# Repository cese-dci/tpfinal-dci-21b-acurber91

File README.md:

## Trabajo Práctico Final de la asignatura DCI ##

Este repositorio contiene el Trabajo Práctico Final de la asignatura de Diseño de Circuitos Impresos de la carrera Maestría en Internet de las Cosas (MIoT) de la FIUBA.

* **Autor**: Agustín Curcio Berardi
* **Revisor**: Gustavo Zocco
* **Docente**: Diego Brengui
* **Título del Trabajo**:  Adafruit Feather M0 with LoRa Radio Module Adaptation
* **Descripción**:  Plataforma modular Feather desarrollada por Adafruit con el mismo concepto de las placas Arduino. Existen diversas placas con un mismo formato físico y diferente hardware montado. Esta versión en particular incorpora un microcontrolador ARM Cortex-M0 junto con un módulo LoRa basado en el chipset SX1276 de la empresa Semtech.

<p align="center">
    <br>
    <b>Figura 1</b>. Vista isométrica superior de la adaptación realizada. 
</p>

<p align="center">
    <br>
    <b>Figura 2</b>. Vista isométrica inferior de la adaptación realizada. 
</p>

<p align="center">
    <br>
    <b>Figura 3</b>. Vista superior de la adaptación realizada. 
</p>

<p align="center">
    <br>
    <b>Figura 4</b>. Vista inferior de la adaptación realizada. 
</p>

## Detalles de la adaptación ##

Este Trabajo Práctico realizó una adaptación de la placa utilizada como propuesta para poder cumplir con los requerimientos establecidos en la materia. Así:

- Se modificaron los tamaños de los componentes pasivos. Se pasó de tamaño 0603 a 0805.
- El cambio de tamaño de los componentes pasivos requirió modificar las dimensiones del circuito impreso. La altura no se modificó para garantizar la compatibilidad con otras placas de la línea Feather. No obstante, sí se modificó el largo total de la misma para hacer lugar a componentes de mayor tamaño. El circuito impreso final es 6,223 mm más largo que el original.
- Se agregó un segundo fiducial que no estaba presente en el diseño original.
- Se adoptó HASL como terminación superficial en lugar de ENIG.

## Licencia de este trabajo ##
Designed by Limor Fried/Ladyada for Adafruit Industries. Creative Commons Attribution/Share-Alike. See License.txt for additional information.

## Estructura ##

El Trabajo Práctico Final tiene la siguiente estructura:

* doc: Toda la información sobre el circuito, principalmente de autoría o procesamiento propio.
  * Notas con cálculos.
  * Fotos de los prototipos.
* info: Toda la información recolectada, principalmente de terceros, como por ejemplo:
  * Hojas de datos.
  * Notas de aplicación.
  * Información de productos comerciales.
* pcb: Archivos de diseño esquemático y PCB.
  * Archivo esquemático en PDF.

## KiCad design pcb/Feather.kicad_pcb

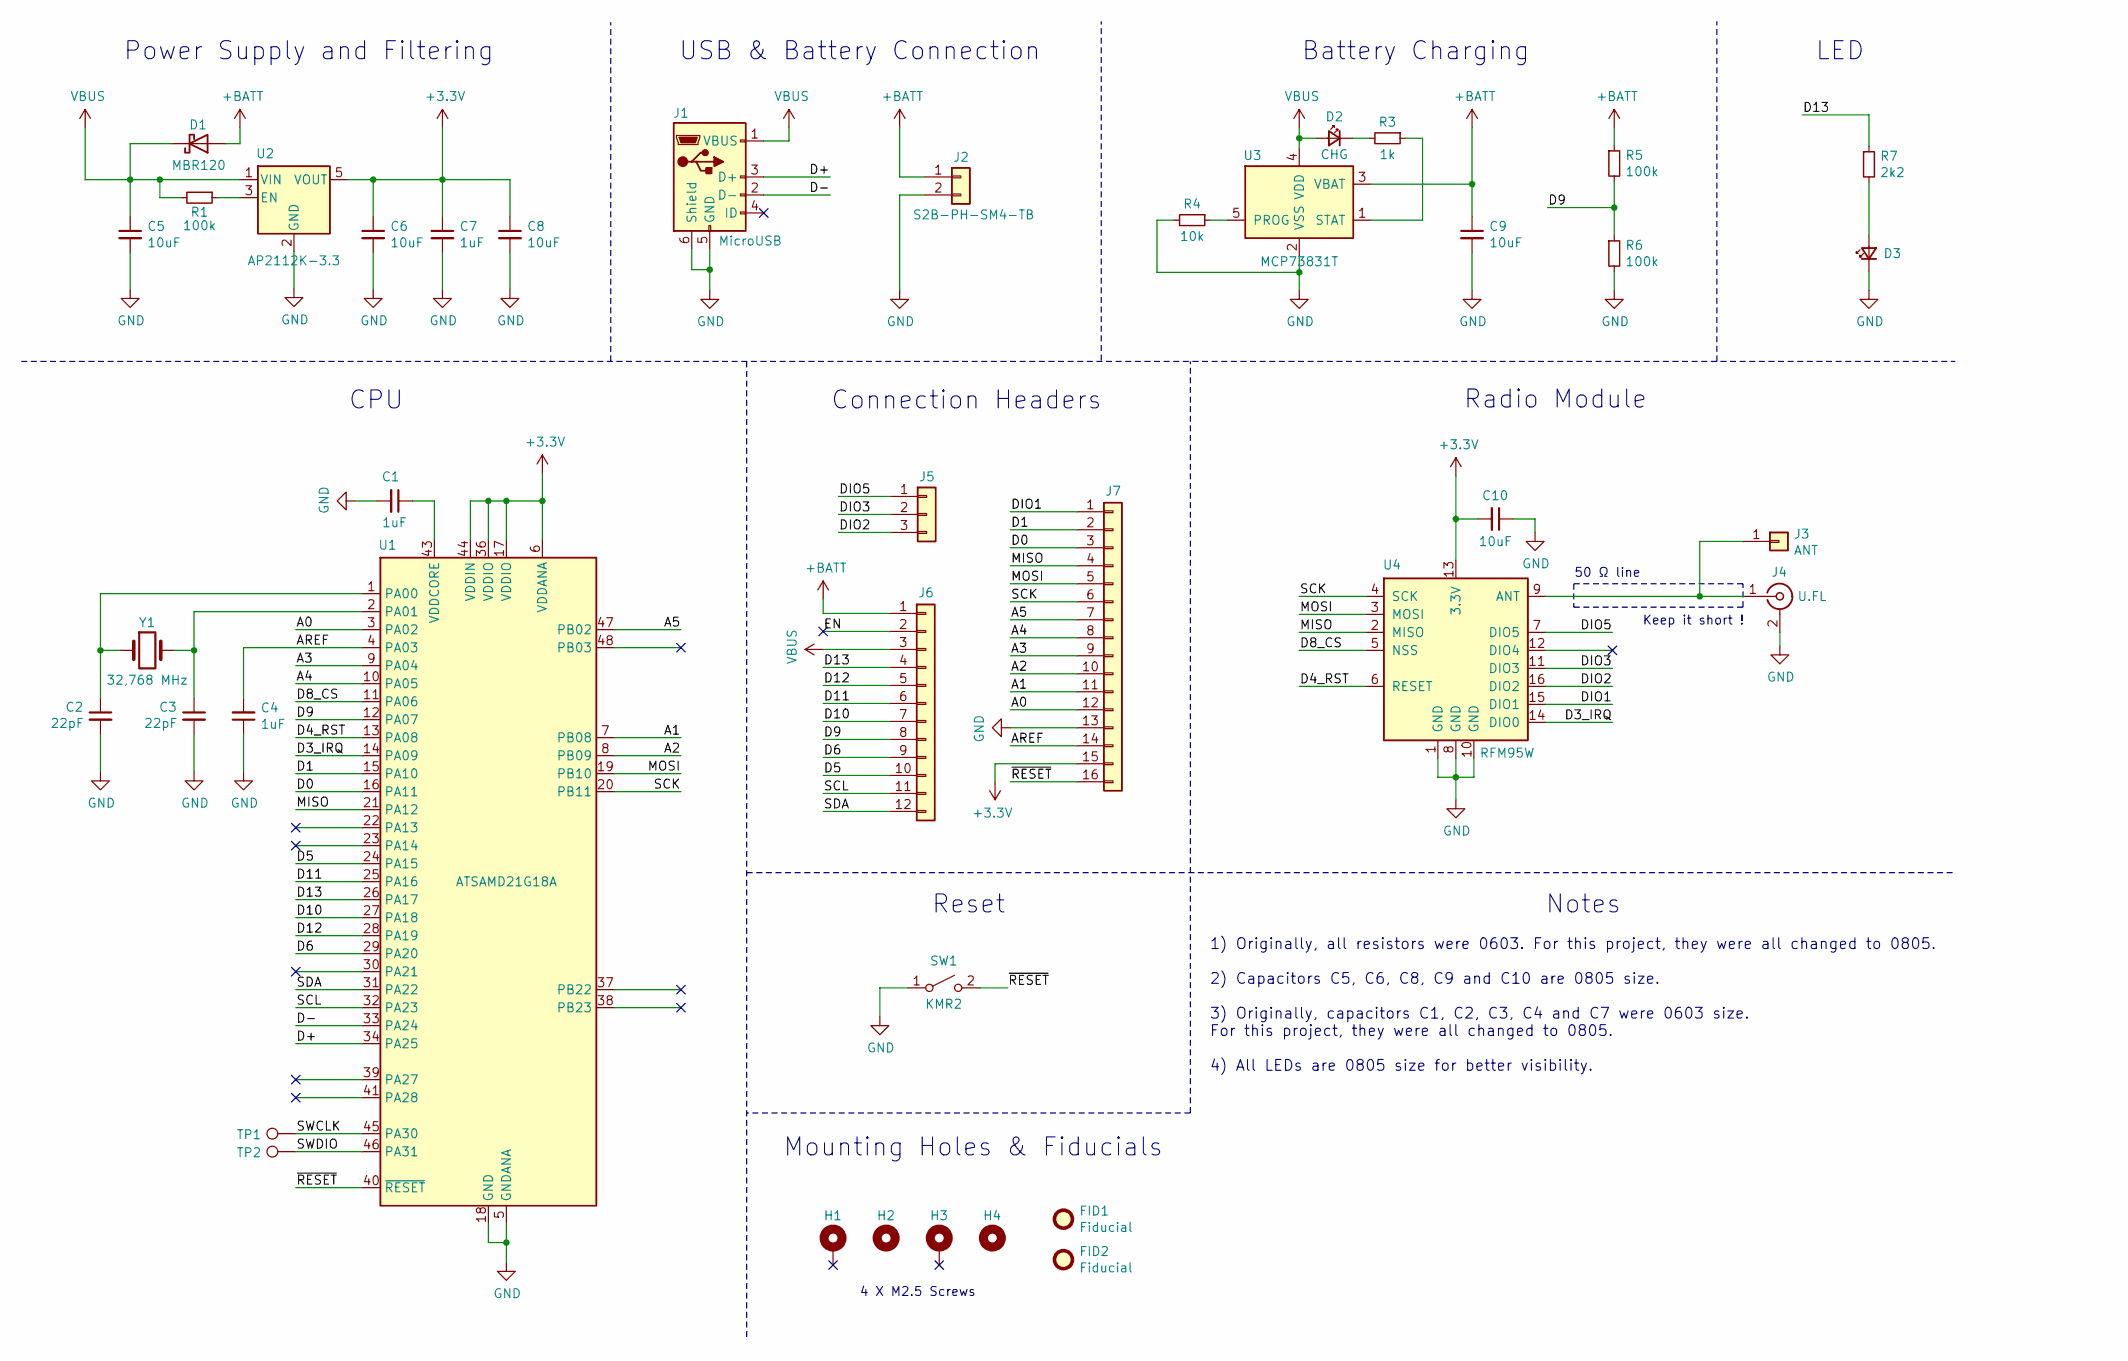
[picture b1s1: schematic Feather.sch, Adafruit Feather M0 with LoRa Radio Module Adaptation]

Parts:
C1, C4, C7: 1uF; C_0805_2012Metric
C2, C3: 22pF; C_0805_2012Metric
C5, C6, C8, C9, C10: 10uF; C_0805_2012Metric
D1: MBR120; D_SOD-123F
D2: CHG; LED_0805_2012Metric_Castellated
D3: PWR; LED_0805_2012Metric_Castellated
FID1, FID2: Fiducial; Fiducial_1mm_Mask2mm
H1, H3: Mounting Hole w/Pad; MountingHole_2.5mm_Pad_TopOnly
H2, H4: Mounting Hole; MountingHole_2.5mm
J1: MicroUSB; USB_Micro-B_Amphenol_10103594-0001LF_Horizontal
J2: S2B-PH-SM4-TB; JST_PH_S2B-PH-SM4-TB_1x02-1MP_P2.00mm_Horizontal
J3: ANT; Adafruit_Feather_PinHeader_1x01_P2.54mm
J4: U.FL; U.FL_Hirose_U.FL-R-SMT-1_Vertical
J5: Conn_01x03; Adafruit_Feather_PinHeader_1x03_P2.54mm
J6: Conn_01x12; Adafruit_Feather_PinHeader_1x12_P2.54mm
J7: Conn_01x16; Adafruit_Feather_PinHeader_1x16_P2.54mm
R1, R5, R6: 100k; R_0805_2012Metric
R3: 1k; R_0805_2012Metric
R4: 10k; R_0805_2012Metric
R7: 2k2; R_0805_2012Metric
SW1: KMR2; SW_Push_1P1T_NO_CK_KMR2
TP1, TP2: TestPoint; TestPoint_Pad_D1.5mm
U1: ATSAMD21G18A; QFN-48-1EP_7x7mm_P0.5mm_EP5.15x5.15mm
U2: AP2112K-3.3; SOT-23-5
U3: MCP73831T; SOT-23-5
U4: RFM95W; HOPERF_RFM9XW_SMD
Y1: 32,768 MHz; Crystal_SMD_3215-2Pin_3.2x1.5mm

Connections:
+3V3: C6.1, C7.1, C8.1, C10.2, J7.15, U1.6 (VDDANA), U1.17 (VDDIO), U1.36 (VDDIO), U1.44 (VDDIN), U2.5 (VOUT), U4.13 (3.3V)
+BATT: C9.1, D1.2 (A), J2.1, J6.1, R5.1, U3.3 (VBAT)
/A0: J7.12, U1.3 (PA02)
/A1: J7.11, U1.7 (PB08)
/A2: J7.10, U1.8 (PB09)
/A3: J7.9, U1.9 (PA04)
/A4: J7.8, U1.10 (PA05)
/A5: J7.7, U1.47 (PB02)
/AREF: C4.2, J7.14, U1.4 (PA03)
/D0: J7.3, U1.16 (PA11)
/D1: J7.2, U1.15 (PA10)
/D3_IRQ: U1.14 (PA09), U4.14 (DIO0)
/D4_RST: U1.13 (PA08), U4.6 (RESET)
/D5: J6.10, U1.24 (PA15)
/D6: J6.9, U1.29 (PA20)
/D8_CS: U1.11 (PA06), U4.5 (NSS)
/D9: J6.8, R5.2, R6.1, U1.12 (PA07)
/D10: J6.7, U1.27 (PA18)
/D11: J6.6, U1.25 (PA16)
/D12: J6.5, U1.28 (PA19)
/D13: J6.4, R7.1, U1.26 (PA17)
/D+: J1.3 (D+), U1.34 (PA25)
/D-: J1.2 (D-), U1.33 (PA24)
/DIO1: J7.1, U4.15 (DIO1)
/DIO2: J5.3, U4.16 (DIO2)
/DIO3: J5.2, U4.11 (DIO3)
/DIO5: J5.1, U4.7 (DIO5)
/EN: J6.2
/MISO: J7.4, U1.21 (PA12), U4.2 (MISO)
/MOSI: J7.5, U1.19 (PB10), U4.3 (MOSI)
/SCK: J7.6, U1.20 (PB11), U4.4 (SCK)
/SCL: J6.11, U1.32 (PA23)
/SDA: J6.12, U1.31 (PA22)
/SWCLK: TP1.1, U1.45 (PA30)
/SWDIO: TP2.1, U1.46 (PA31)
/~RESET: J7.16, SW1.2 (B), U1.40 (~RESET)
GND: C1.2, C2.2, C3.2, C4.1, C5.2, C6.2, C7.2, C8.2, C9.2, C10.1, D3.1 (K), J1.5 (GND), J1.6 (Shield), J2.2, J4.2 (Ext), J7.13, R4.2, R6.2, SW1.1 (A), U1.5 (GNDANA), U1.18 (GND), U1.35 (GND), U1.42 (GND), U1.49 (EP), U2.2 (GND), U3.2 (VSS), U4.1 (GND), U4.8 (GND), U4.10 (GND)
unnamed: C1.1, U1.43 (VDDCORE)
unnamed: C2.1, U1.1 (PA00), Y1.1
unnamed: C3.1, U1.2 (PA01), Y1.2
unnamed: D2.1 (K), R3.2
unnamed: D3.2 (A), R7.2
unnamed: J3.1, J4.1 (In), U4.9 (ANT)
unnamed: R1.1, U2.3 (EN)
unnamed: R3.1, U3.1 (STAT)
unnamed: R4.1, U3.5 (PROG)
VBUS: C5.1, D1.1 (K), D2.2 (A), J1.1 (VBUS), J6.3, R1.2, U2.1 (VIN), U3.4 (VDD)

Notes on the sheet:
USB & Battery Connection
Battery Charging
LED
CPU
Connection Headers
Radio Module
1) Originally, all resistors were 0603. For this project, they were all changed to 0805. 2) Capacitors C5, C6, C8, C9 and C10 are 0805 size. 3) Originally, capacitors C1, C2, C3, C4 and C7 were 0603 size. For this project, they were all changed to 0805. 4) All LEDs are 0805 size for better visibili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
Notes
Keep it short !
50 Ω line
Power Supply and Filtering
Reset
Mounting Holes & Fiducials
4 X M2.5 Screws

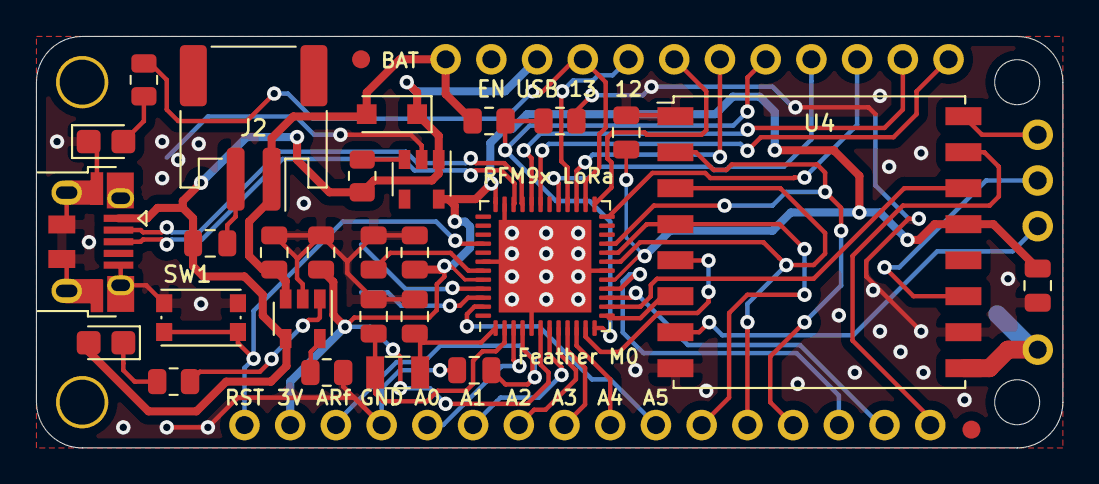
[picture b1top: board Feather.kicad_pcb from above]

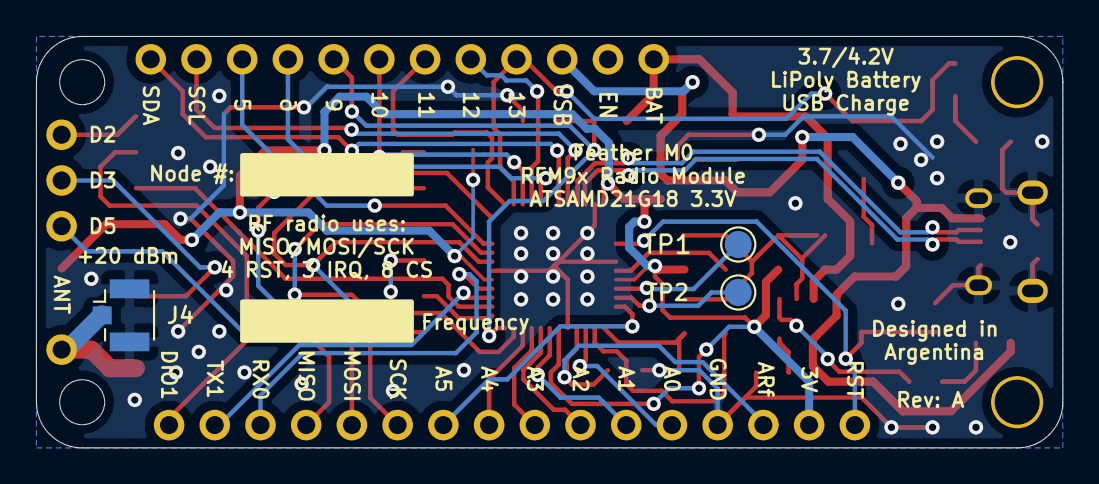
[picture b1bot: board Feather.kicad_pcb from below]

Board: 2 copper layers, 57.0 x 22.9 mm, 40 parts (3 on the bottom side), 46 nets.

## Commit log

2021-06-26 En este commit inicial se agrega el esquemático completo de la placa Adafruit Feather M0 junto con las hojas de datos de sus principales componentes.
2021-06-27 Se agregan los modelos 3D que estaban faltando así como también la documentación y hojas de datos faltantes.
2021-06-27 Se crea la biblioteca Adafruit_PinHeader para las tiras de pines que se deben soldar en los costados de la placa. Con esta modificación, se actualizo también el circuito esquemático. Listo para corre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
2021-06-28 Se realizan leves ajustes en el esquemático y se adiciona el archivo de licencia. Listo para revisar.
2021-06-28 Se agrega el esquemático en formato PDF para facilitar su revisión.
2021-07-30 Se modifica todo el proyecto para utilizar componentes 0805 en lugar de 0603 que se usan en el circuito original. Se incorpora archivo del PCB, con componentes posicionados y con modelos 3D incluídos.
2021-08-09 Se hicieron más ajustes para acomodar mejor los componentes tamaño 0805 no contemplados al comienzo del posicionamiento.
2021-08-09 Se agrega margen en el circuito a 0,5 mm del borde de placa.
2021-08-11 Se corrigen las observaciones realizadas por el docente. Adicionalmente se sube el ruteo de la placa.
2021-08-11 Se modifica la CPW de la línea de antena y se agrega el cálculo.
2021-08-16 Últimos retoques en el PCB de acuerdo a las correcciones realizadas.
2021-08-16 Se agrega el README de la propuesta.
2021-08-16 Se modifica el README principal del Trabajo.
2021-08-16 Se agregan imágenes al README principal del Trabajo.
2021-08-16 Se agregó un README con los cálculos de líneas de transmisión.
2021-08-16 Se agregaron cálculos de líneas con impedancia controlada.
2021-08-16 Se agrega detalle de adaptaciones realizadas en el archivo README.md principal.
2021-08-16 Se modifica el tamaño de la fotografía de vista superior para que sea igual a la del lado inferior.
2021-08-16 Modificación de imagen superior.
2021-08-16 Se actualizan los archivos PDF del esquemático y circuito impreso.
2021-08-16 Se elimina README de la sección PCB.
2021-08-16 Leves ajustes en el texto aclaratorio del PCB.
2021-08-16 Se agregaron algunas regiones de 'keep out' en el cobre superior para mejorar la prolijidad del circuito.
2021-08-16 Se realizaron ajustes a los 'keep outs' de la capa de cobre superior.
2021-08-17 Se agregaron todos los componentes 3D de las bibliotecas de KiCAD al proyecto.
